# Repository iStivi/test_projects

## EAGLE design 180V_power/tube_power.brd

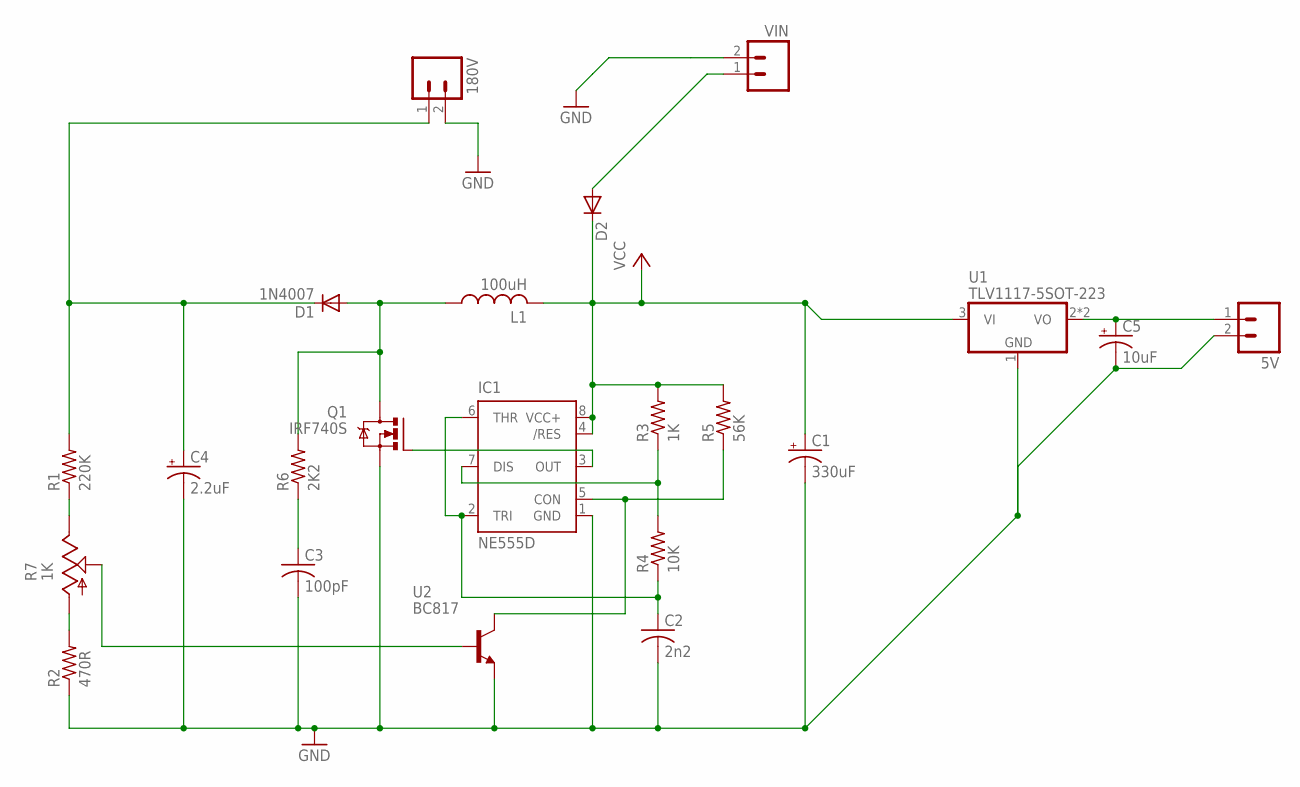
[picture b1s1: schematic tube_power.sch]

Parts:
5V, 180V: M023.5MM; SCREWTERMINAL-3.5MM-2
C1: 330uF; E5-10,5
C2: 2n2; C0805K
C3: 100pF; C0805K
C4: 2.2uF; E5-10,5
C5: 10uF; E2-5
D1: 1N4007; SMA-DIODE
D2: DIODESMA; SMA-DIODE
IC1: NE555D; SO08
L1: 100uH; RBL0712
Q1: IRF740S; TO263
R1: 220K; 0207/10
R2: 470R; 0207/10
R3: 1K; R0805
R4: 10K; R0805
R5: 56K; R0805
R6: 2K2; R0805
R7: 1K; CA6V
U1: TLV1117-5SOT-223; SOT-223
U2: BC817; SOT-23
VIN: M023.5MM; SCREWTERMINAL-3.5MM-2

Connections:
5V: 5V.1, C5.+, U1.2 (VO), U1.4 (VO)
180V: 180V.1, C4.+, D1.C, R1.2
CON: IC1.5 (CON), R5.1, U2.3 (C)
DIS: IC1.7 (DIS), R3.1, R4.2
GND: 5V.2, 180V.2, C1.-, C2.2, C3.2, C4.-, C5.-, IC1.1 (GND), Q1.2 (S), R2.1, U1.1 (GND), U2.2 (E), VIN.2
L1: D1.A, L1.P$1 (1), Q1.3 (D), R6.2
unnamed: D2.A, VIN.1
OUT: IC1.3 (OUT), Q1.1 (G)
R1: R1.1, R7.E
R2: R2.2, R7.A
R6: C3.1, R6.1
THR: C2.1, IC1.2 (TRI), IC1.6 (THR), R4.1
VAR: R7.S, U2.1 (B)
VCC: C1.+, D2.C, IC1.4 (/RES), IC1.8 (VCC+), L1.P$2 (2), R3.2, R5.2, U1.3 (VI)

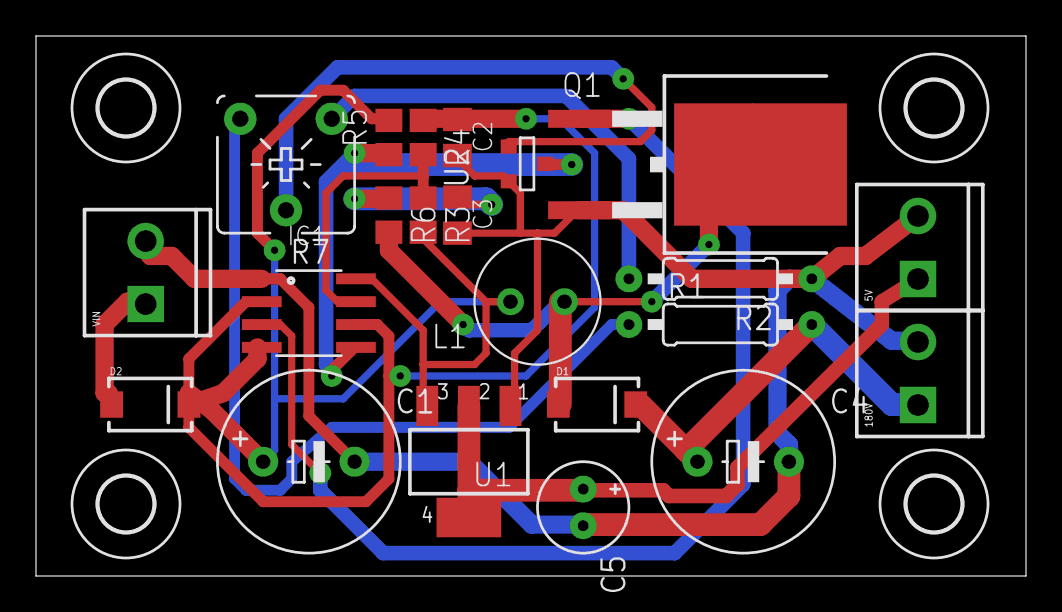
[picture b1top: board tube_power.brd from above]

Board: 2 copper layers, 55.0 x 30.0 mm, 28 parts (1 on the bottom side), 14 nets.

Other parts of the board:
U$1, U$2, U$4, U$5: 3,0-SMALL
U$3: BUZZBOY-SILK
U$6: BUZZBOY

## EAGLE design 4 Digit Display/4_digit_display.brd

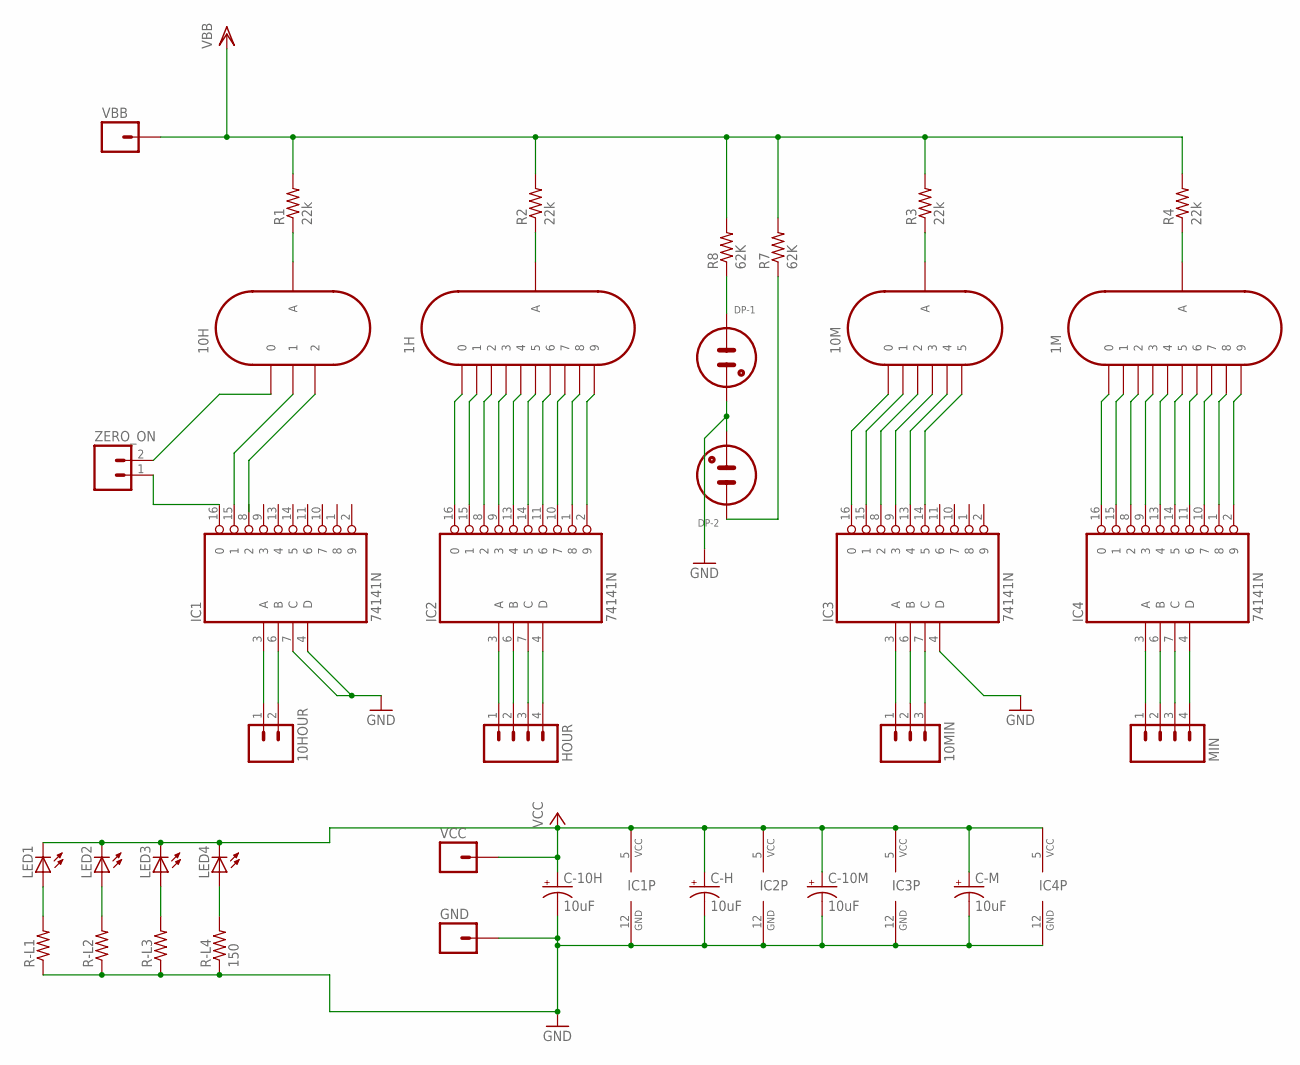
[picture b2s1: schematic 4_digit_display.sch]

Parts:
1H, 1M: IN-12A-NO_DP; IN-12_NO-DP
10H: IN-12_2DIGIT
10HOUR: M02PTH; 1X02
10M: IN-12_6DIGIT
10MIN: M03PTH; 1X03
C-10H, C-10M: 10uF; B/3528-21R
C-H: 10uF; B/3528-21R
C-M: 10uF; B/3528-21R
DP-1, DP-2: INS-1
GND: M01PTH; 1X01
HOUR: M04PTH; 1X04
IC1, IC2, IC3, IC4: 74141N; DIL16
LED1, LED2, LED3, LED4: LED1210
MIN: M04PTH; 1X04
R1, R2, R3, R4: 22k; 0207/10
R7, R8: 62K; 0207/10
R-L1, R-L2, R-L3: RESISTORR1206; R1206
R-L4: 150; R1206
VBB: M01PTH; 1X01
VCC: M01PTH; 1X01
ZERO_ON: M02PTH; 1X02

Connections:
GND: C-10H.-, C-10M.-, C-H.-, C-M.-, DP-1.K, DP-2.K, GND.1, IC1.4 (D), IC1.7 (C), IC1.12 (GND), IC2.12 (GND), IC3.4 (D), IC3.12 (GND), IC4.12 (GND), R-L1.1, R-L2.1, R-L3.1, R-L4.1
unnamed: 1M.0, IC4.16 (0)
unnamed: 1M.1, IC4.15 (1)
unnamed: 1M.2, IC4.8 (2)
unnamed: 1M.3, IC4.9 (3)
unnamed: 1M.4, IC4.13 (4)
unnamed: 1M.5, IC4.14 (5)
unnamed: 1M.6, IC4.11 (6)
unnamed: 1M.7, IC4.10 (7)
unnamed: 1M.8, IC4.1 (8)
unnamed: 1M.9, IC4.2 (9)
unnamed: 10M.0, IC3.16 (0)
unnamed: 10M.1, IC3.15 (1)
unnamed: 10M.2, IC3.8 (2)
unnamed: 10M.3, IC3.9 (3)
unnamed: 10M.4, IC3.13 (4)
unnamed: 10M.5, IC3.14 (5)
unnamed: 1H.0, IC2.16 (0)
unnamed: 1H.1, IC2.15 (1)
unnamed: 1H.2, IC2.8 (2)
unnamed: 1H.3, IC2.9 (3)
unnamed: 1H.4, IC2.13 (4)
unnamed: 1H.5, IC2.14 (5)
unnamed: 1H.6, IC2.11 (6)
unnamed: 1H.7, IC2.10 (7)
unnamed: 1H.8, IC2.1 (8)
unnamed: 1H.9, IC2.2 (9)
unnamed: 10H.1, IC1.15 (1)
unnamed: DP-1.A, R8.1
unnamed: DP-2.A, R7.1
unnamed: IC4.3 (A), MIN.1
unnamed: 1M.A, R4.1
unnamed: 10M.A, R3.1
unnamed: 1H.A, R2.1
unnamed: 10H.A, R1.1
unnamed: IC4.6 (B), MIN.2
unnamed: IC4.7 (C), MIN.3
unnamed: IC4.4 (D), MIN.4
unnamed: 10MIN.1, IC3.3 (A)
unnamed: 10MIN.2, IC3.6 (B)
unnamed: 10MIN.3, IC3.7 (C)
unnamed: HOUR.1, IC2.3 (A)
unnamed: HOUR.2, IC2.6 (B)
unnamed: HOUR.3, IC2.7 (C)
unnamed: HOUR.4, IC2.4 (D)
unnamed: 10HOUR.1, IC1.3 (A)
unnamed: 10HOUR.2, IC1.6 (B)
unnamed: IC1.16 (0), ZERO_ON.1
unnamed: 10H.0, ZERO_ON.2
unnamed: LED1.A, R-L1.2
unnamed: LED2.A, R-L2.2
unnamed: LED3.A, R-L3.2
unnamed: LED4.A, R-L4.2
VBB: R1.2, R2.2, R3.2, R4.2, R7.2, R8.2, VBB.1
VCC: C-10H.+, C-10M.+, C-H.+, C-M.+, IC1.5 (VCC), IC2.5 (VCC), IC3.5 (VCC), IC4.5 (VCC), LED1.C, LED2.C, LED3.C, LED4.C, VCC.1

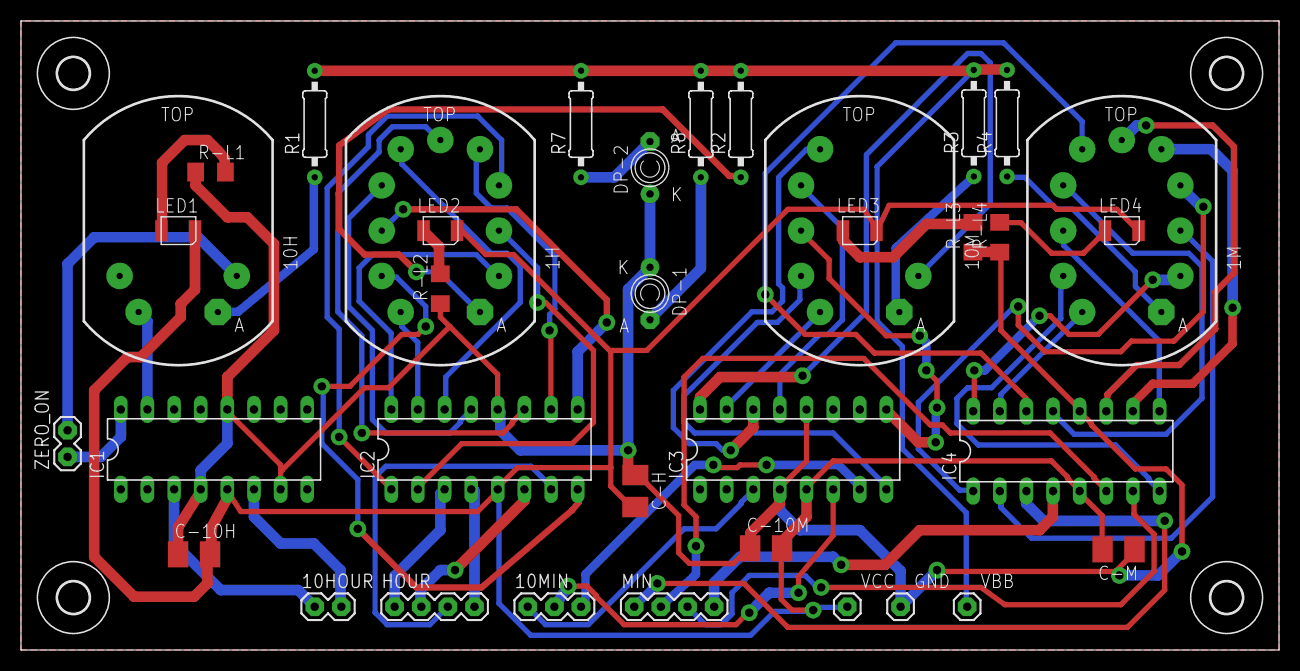
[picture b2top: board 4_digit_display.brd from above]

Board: 2 copper layers, 120.0 x 60.0 mm, 40 parts (0 on the bottom side), 55 nets.

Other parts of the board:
U$2, U$3, U$4, U$5: 3,0

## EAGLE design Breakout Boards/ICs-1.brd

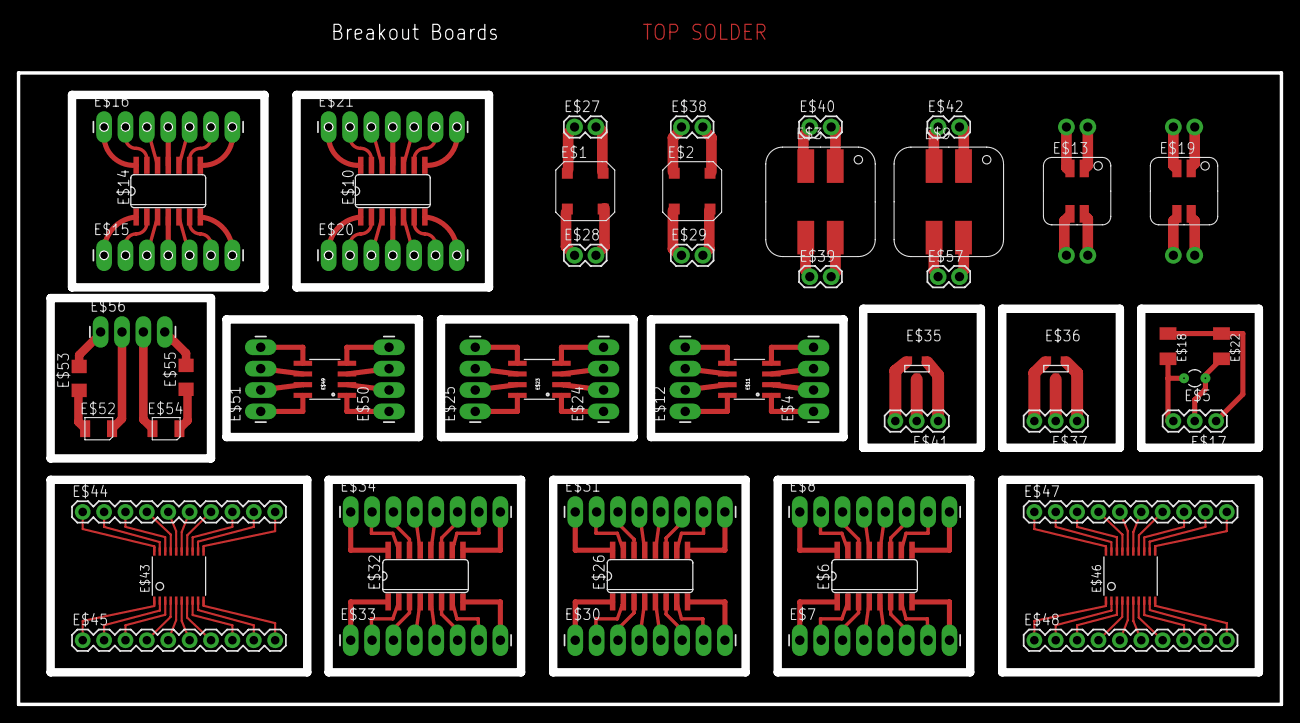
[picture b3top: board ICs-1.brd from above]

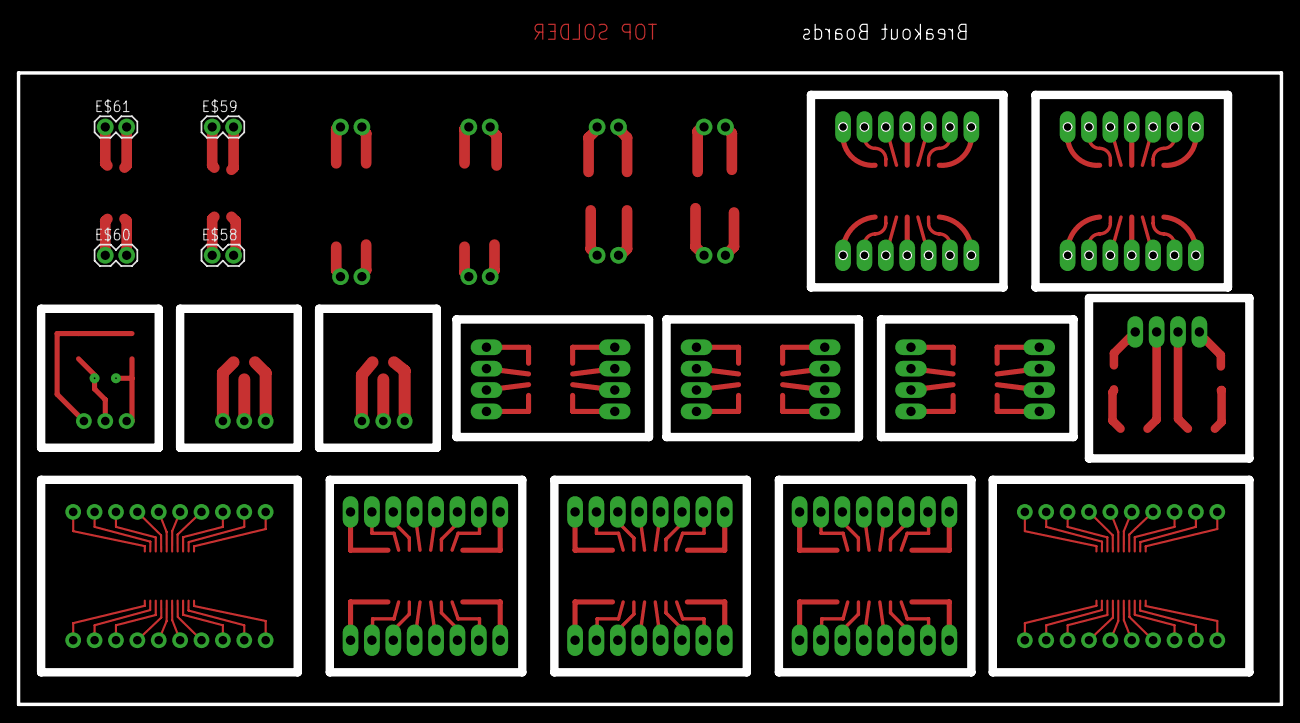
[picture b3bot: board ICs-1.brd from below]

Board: 2 copper layers, 150.0 x 75.0 mm, 61 parts (4 on the bottom side), 129 nets.

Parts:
E$1, E$2: LPR6235
E$3, E$9: MSD1260
E$4, E$12, E$24, E$25, E$50, E$51, E$56: 1X04_LONGPADS
E$5: TC26V
E$6, E$26, E$32: SO16
E$7, E$8, E$30, E$31, E$33, E$34: 1X08_LONGPADS
E$10, E$14: SO14
E$11, E$23, E$49: SO08
E$13, E$19: MSD7342
E$15, E$16, E$20, E$21: 1X07_LONGPADS
E$17, E$37, E$41: 1X03
E$18, E$22: C1206K
E$27, E$28, E$29, E$38, E$39, E$40, E$42, E$57, E$58, E$59, E$60, E$61: 1X02
E$35, E$36: SOT-23
E$43, E$46: TSSOP20
E$44, E$45, E$47, E$48: 1X10
E$52, E$54: LED1210
E$53, E$55: R1206

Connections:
S$15: E$14.1, E$15.1
S$16: E$14.2, E$15.2
S$17: E$6.16, E$8.1
S$18: E$6.15, E$8.2
S$19: E$6.14, E$8.3
S$20: E$6.13, E$8.4
S$21: E$6.12, E$8.5
S$22: E$6.11, E$8.6
S$23: E$6.10, E$8.7
S$24: E$6.9, E$8.8
S$25: E$6.1, E$7.1
S$26: E$6.2, E$7.2
S$27: E$6.3, E$7.3
S$28: E$6.4, E$7.4
S$29: E$6.5, E$7.5
S$30: E$6.7, E$7.7
S$31: E$6.6, E$7.6
S$32: E$6.8, E$7.8
S$33: E$17.3, E$18.2
S$34: E$17.2, E$22.2
S$35: E$17.1, E$18.1, E$22.1
S$36: E$14.3, E$15.3
S$37: E$14.4, E$15.4
S$39: E$14.5, E$15.5
S$40: E$14.6, E$15.6
S$49: E$14.7, E$15.7
S$50: E$14.14, E$16.1
S$51: E$14.13, E$16.2
S$52: E$14.12, E$16.3
S$53: E$14.11, E$16.4
S$54: E$14.10, E$16.5
S$55: E$14.9, E$16.6
S$56: E$14.8, E$16.7
S$57: E$23.8, E$25.1
S$58: E$23.7, E$25.2
S$59: E$23.6, E$25.3
S$60: E$23.5, E$25.4
S$61: E$23.1, E$24.1
S$62: E$23.2, E$24.2
S$63: E$11.8, E$12.1
S$64: E$11.7, E$12.2
S$65: E$11.6, E$12.3
S$66: E$11.5, E$12.4
S$67: E$4.1, E$11.1
S$68: E$4.2, E$11.2
S$69: E$4.3, E$11.3
S$70: E$4.4, E$11.4
S$91: E$10.1, E$20.1
S$92: E$10.2, E$20.2
S$93: E$10.3, E$20.3
S$94: E$10.4, E$20.4
S$95: E$10.5, E$20.5
S$96: E$10.6, E$20.6
S$97: E$10.7, E$20.7
S$98: E$10.14, E$21.1
S$99: E$10.13, E$21.2
S$100: E$10.12, E$21.3
S$101: E$10.11, E$21.4
S$102: E$10.10, E$21.5
S$103: E$10.9, E$21.6
S$104: E$10.8, E$21.7
S$105: E$23.3, E$24.3
S$106: E$23.4, E$24.4
S$108: E$26.16, E$31.1
S$109: E$26.15, E$31.2
S$110: E$26.14, E$31.3
S$111: E$26.13, E$31.4
S$123: E$26.12, E$31.5
S$124: E$26.11, E$31.6
S$125: E$26.10, E$31.7
S$126: E$26.9, E$31.8
S$127: E$26.1, E$30.1
S$128: E$26.2, E$30.2
S$129: E$26.3, E$30.3
S$130: E$26.4, E$30.4
S$131: E$26.5, E$30.5
S$132: E$26.7, E$30.7
S$133: E$26.6, E$30.6
S$134: E$26.8, E$30.8
S$135: E$32.16, E$34.1
S$136: E$32.15, E$34.2
S$137: E$32.14, E$34.3
S$138: E$32.13, E$34.4
S$139: E$32.12, E$34.5
S$140: E$32.11, E$34.6
S$141: E$32.10, E$34.7
S$142: E$32.9, E$34.8
S$143: E$32.1, E$33.1
S$144: E$32.2, E$33.2
S$145: E$32.3, E$33.3
S$146: E$32.4, E$33.4
S$147: E$32.5, E$33.5
S$148: E$32.7, E$33.7
S$149: E$32.6, E$33.6
S$150: E$32.8, E$33.8
S$157: E$43.20, E$44.1
S$158: E$43.19, E$44.2
S$159: E$43.18, E$44.3
S$160: E$43.17, E$44.4
S$161: E$43.16, E$44.5
S$162: E$43.15, E$44.6
S$163: E$43.14, E$44.7
S$164: E$43.12, E$44.9
S$165: E$43.13, E$44.8
S$166: E$43.11, E$44.10
S$167: E$46.20, E$47.1
S$168: E$46.19, E$47.2
S$169: E$46.18, E$47.3
S$170: E$46.17, E$47.4
S$171: E$46.16, E$47.5
S$172: E$46.15, E$47.6
S$173: E$46.14, E$47.7
S$174: E$46.12, E$47.9
S$175: E$46.13, E$47.8
S$176: E$46.11, E$47.10
S$197: E$49.8, E$51.1
S$198: E$49.7, E$51.2
S$199: E$49.6, E$51.3
S$200: E$49.5, E$51.4
S$201: E$49.1, E$50.1
S$202: E$49.2, E$50.2
S$203: E$49.3, E$50.3
S$204: E$49.4, E$50.4
S$205: E$53.2, E$56.1
S$206: E$52.A, E$53.1
S$207: E$52.C, E$56.2
S$208: E$54.A, E$56.3
S$209: E$54.C, E$55.1
S$210: E$55.2, E$56.4

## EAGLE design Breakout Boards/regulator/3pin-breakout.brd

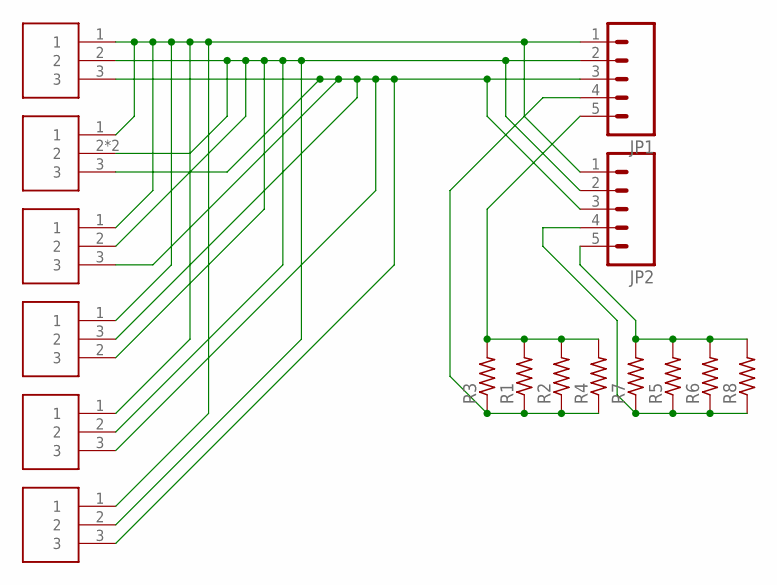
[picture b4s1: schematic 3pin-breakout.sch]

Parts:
JP1, JP2: M05PTH; 1X05
R1, R3, R5, R7: RESISTORR0805; R0805
R2, R4, R6, R8: RESISTORR1206; R1206
U$1: BLANK-3PINSOT23; SOT-23
U$2: BLANK-3PINSOT223; SOT-223
U$3: BLANK-3PINSOT323; SC70
U$4: BLANK-3PINSOT416; SC75_INFINEON
U$5: BLANK-3PINTO252; TO252
U$6: BLANK-3PINTO263; TO263

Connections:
unnamed: JP1.1, JP2.1, U$1.1, U$2.1, U$3.1, U$4.1, U$5.1, U$6.1
unnamed: JP1.2, JP2.2, U$1.2, U$2.2, U$2.4 (2), U$3.2, U$4.2 (3), U$5.2, U$6.2
unnamed: JP1.3, JP2.3, U$1.3, U$2.3, U$3.3, U$4.3 (2), U$5.3, U$6.3
unnamed: JP1.5, R1.2, R2.2, R3.2, R4.2
unnamed: JP1.4, R1.1, R2.1, R3.1, R4.1
unnamed: JP2.5, R5.2, R6.2, R7.2, R8.2
unnamed: JP2.4, R5.1, R6.1, R7.1, R8.1

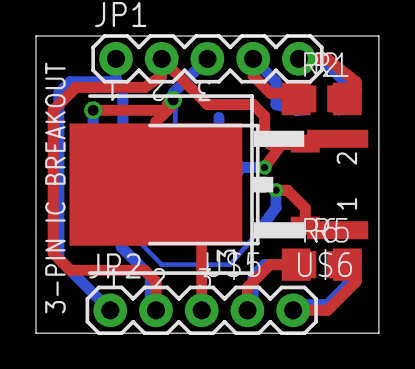
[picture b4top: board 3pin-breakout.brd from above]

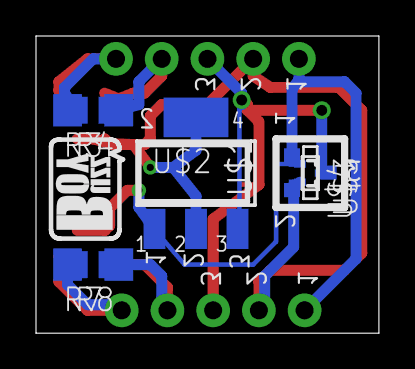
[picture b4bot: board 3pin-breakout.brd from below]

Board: 2 copper layers, 19.1 x 16.5 mm, 17 parts (8 on the bottom side), 7 nets.

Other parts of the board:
U$7: BUZZBOY-SILK-BOTTOM

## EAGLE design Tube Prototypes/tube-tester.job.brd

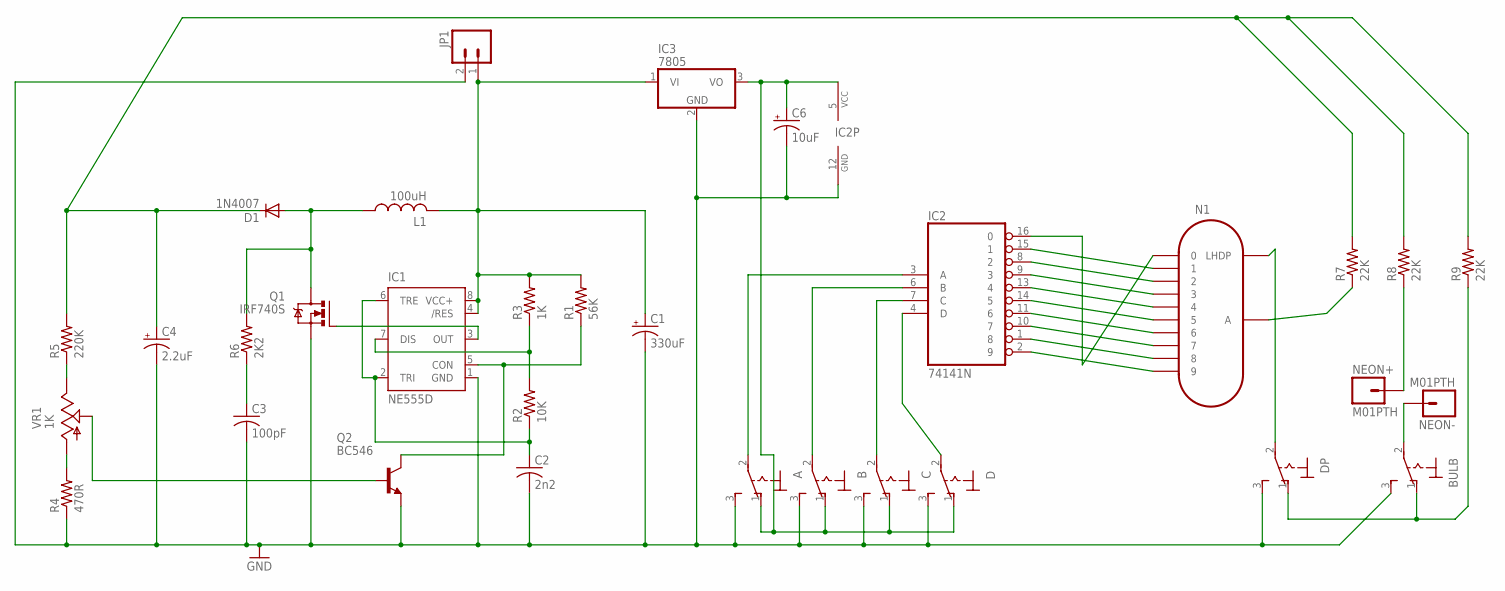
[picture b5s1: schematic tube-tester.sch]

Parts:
A: 320-916
B: 320-916
BULB: 320-916
C: 320-916
C1: 330uF; E5-10,5
C2: 2n2; C1206K
C3: 100pF; C1206K
C4: 2.2uF; E3,5-8
C6: 10uF; E2-5
D: 320-916
D1: 1N4007; SMA-DIODE
DP: 320-916
IC1: NE555D; SO08
IC2: 74141N; DIL16
IC3: 7805; TO220H
JP1: M023.5MM; SCREWTERMINAL-3.5MM-2
L1: 100uH; 0207/10
N1: IN-12B; IN-12
NEON+: M01PTH; 1X01
NEON-: M01PTH; 1X01
Q1: IRF740S; TO263
Q2: BC546; TO92-EBC
R1: 56K; R1206
R2: 10K; R1206
R3: 1K; R1206
R4: 470R; 0207/10
R5: 220K; 0207/10
R6: 2K2; R1206
R7, R8, R9: 22K; 0207/10
VR1: 1K; CA6V

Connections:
GND: A.3 (S), B.3 (S), BULB.3 (S), C.3 (S), C1.-, C2.2, C3.2, C4.-, C6.-, D.3 (S), DP.3 (S), IC1.1 (GND), IC2.12 (GND), IC3.2 (GND), JP1.2, Q1.2 (S), Q2.E, R4.1
unnamed: IC1.3 (OUT), Q1.1 (G)
unnamed: C3.1, R6.1
unnamed: IC1.5 (CON), Q2.C, R1.1
unnamed: IC1.7 (DIS), R2.2, R3.1
unnamed: C2.1, IC1.2 (TRI), IC1.6 (TRE), R2.1
unnamed: D1.A, L1.1, Q1.3 (D), R6.2
unnamed: C4.+, D1.C, R5.2, R7.2, R8.2, R9.2
unnamed: R5.1, VR1.E
unnamed: R4.2, VR1.A
unnamed: Q2.B, VR1.S
unnamed: IC2.15 (1), N1.1
unnamed: IC2.8 (2), N1.2
unnamed: IC2.9 (3), N1.3
unnamed: IC2.13 (4), N1.4
unnamed: IC2.14 (5), N1.5
unnamed: IC2.11 (6), N1.6
unnamed: IC2.10 (7), N1.7
unnamed: IC2.1 (8), N1.8
unnamed: IC2.2 (9), N1.9
unnamed: IC2.16 (0), N1.0
unnamed: N1.A, R7.1
unnamed: A.2, IC2.3 (A)
unnamed: B.2, IC2.6 (B)
unnamed: C.2, IC2.7 (C)
unnamed: D.2, IC2.4 (D)
unnamed: C1.+, IC1.4 (/RES), IC1.8 (VCC+), IC3.1 (VI), JP1.1, L1.2, R1.2, R3.2
unnamed: NEON+.1, R8.1
unnamed: BULB.2, NEON-.1
unnamed: A.1 (O), B.1 (O), C.1 (O), C6.+, D.1 (O), IC2.5 (VCC), IC3.3 (VO)
unnamed: DP.2, N1.LHDP
unnamed: BULB.1 (O), DP.1 (O), R9.1

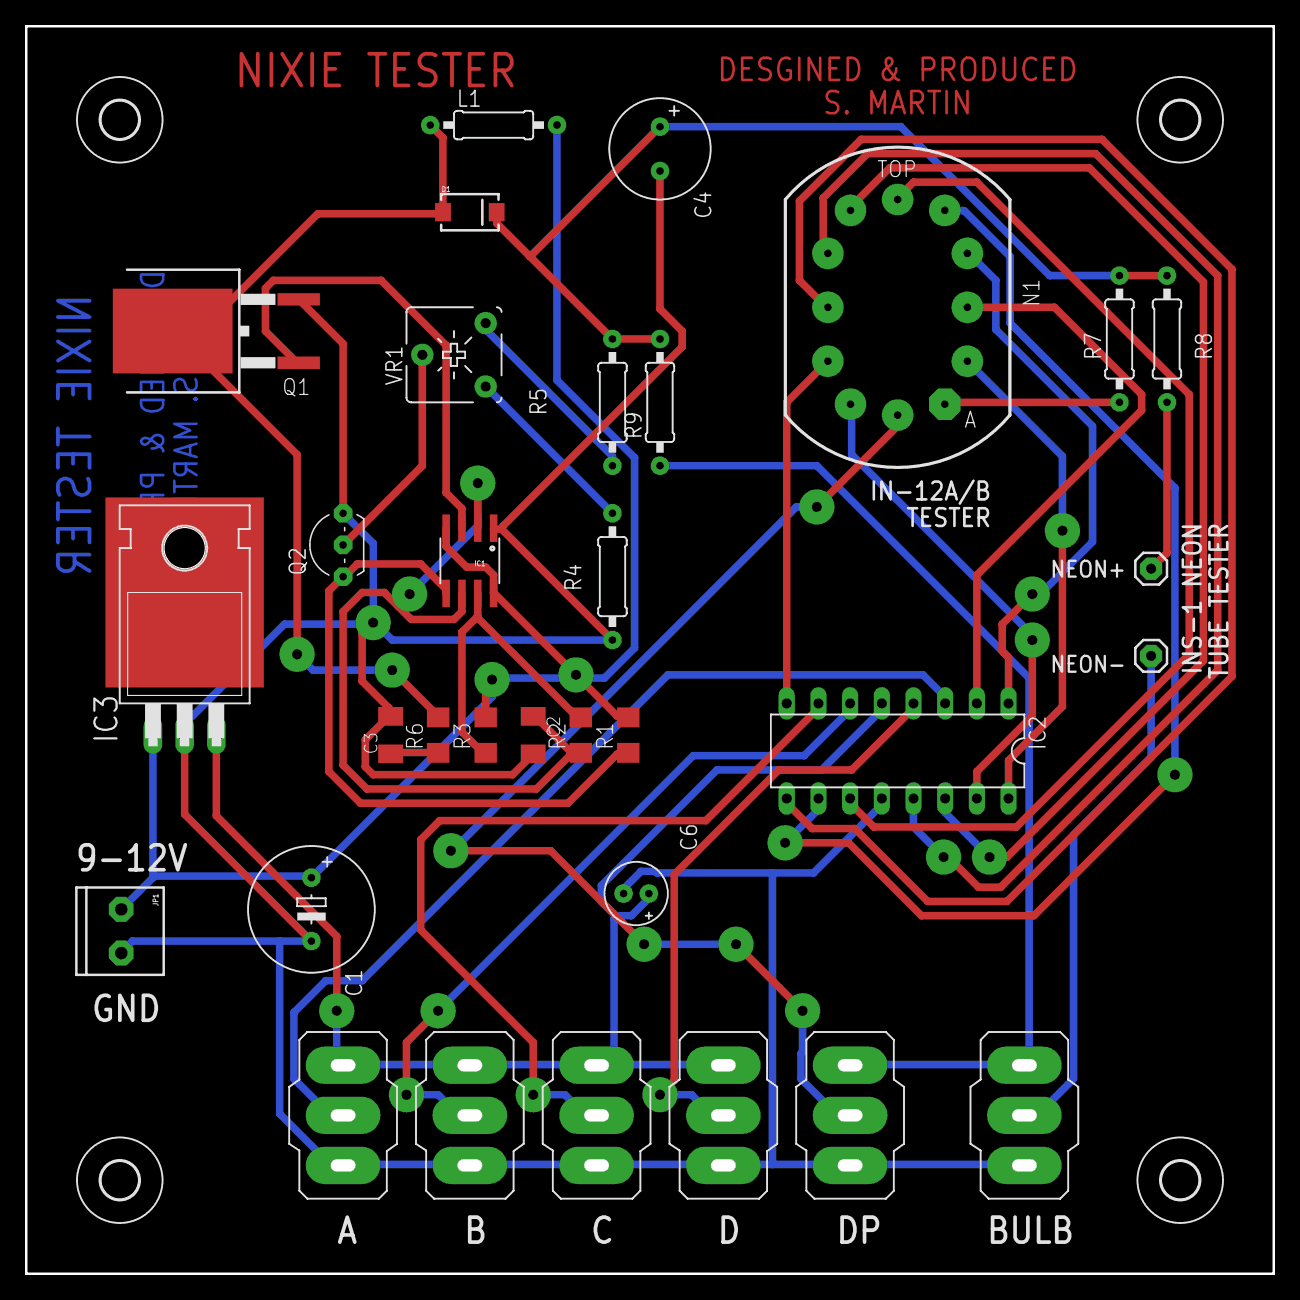
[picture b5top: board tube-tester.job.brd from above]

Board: 2 copper layers, 100.0 x 100.0 mm, 36 parts (0 on the bottom side), 32 nets.

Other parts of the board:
U$1, U$2, U$3, U$4: 3,0

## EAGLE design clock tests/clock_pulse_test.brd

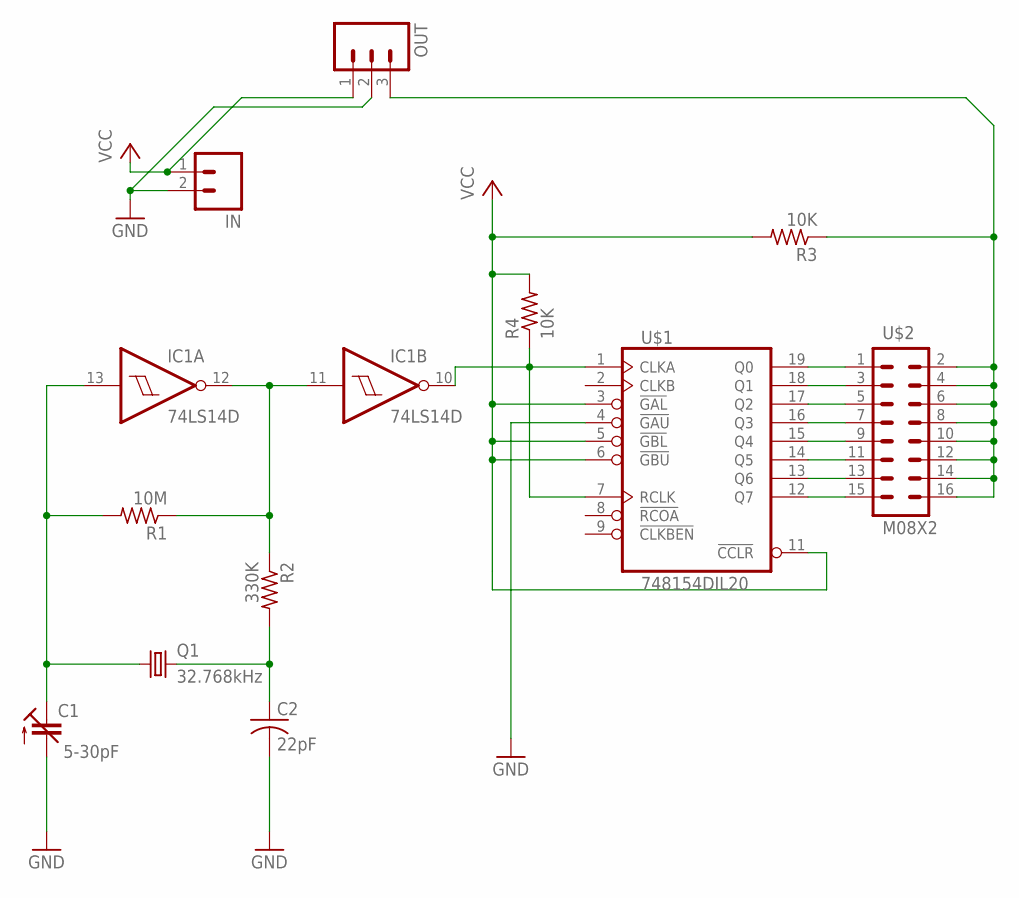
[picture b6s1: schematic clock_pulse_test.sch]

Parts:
C1: 5-30pF; CTRIMTZ03
C2: 22pF; C050-024X044
IC1: 74LS14D; SO14
IN: M02PTH; 1X02
OUT: M03PTH; 1X03
Q1: 32.768kHz; TC26V
R1: 10M; 0207/10
R2: 330K; 0207/10
R3, R4: 10K; 0207/10
U$1: 748154DIL20; DIL20
U$2: M08X2; 2X8

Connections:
GND: C1.2 (A), C2.2, IC1.7 (GND), IN.2, OUT.2, U$1.4 (!GAU), U$1.10 (GND)
unnamed: U$1.19 (Q0), U$2.1
unnamed: U$1.18 (Q1), U$2.3
unnamed: U$1.17 (Q2), U$2.5
unnamed: U$1.16 (Q3), U$2.7
unnamed: U$1.15 (Q4), U$2.9
unnamed: U$1.14 (Q5), U$2.11
unnamed: U$1.13 (Q6), U$2.13
unnamed: U$1.12 (Q7), U$2.15
unnamed: C1.1 (E), IC1.13 (I), Q1.1, R1.2
unnamed: C2.1, Q1.2, R2.2
unnamed: IC1.11 (I), IC1.12 (O), R1.1, R2.1
unnamed: IC1.10 (O), R4.1, U$1.1 (CLKA), U$1.7 (RCLK)
unnamed: OUT.3, R3.1, U$2.2, U$2.4, U$2.6, U$2.8, U$2.10, U$2.12, U$2.14, U$2.16
VCC: IC1.14 (VCC), IN.1, OUT.1, R3.2, R4.2, U$1.3 (!GAL), U$1.5 (!GBL), U$1.6 (!GBU), U$1.11 (!CCLR), U$1.20 (VCC)

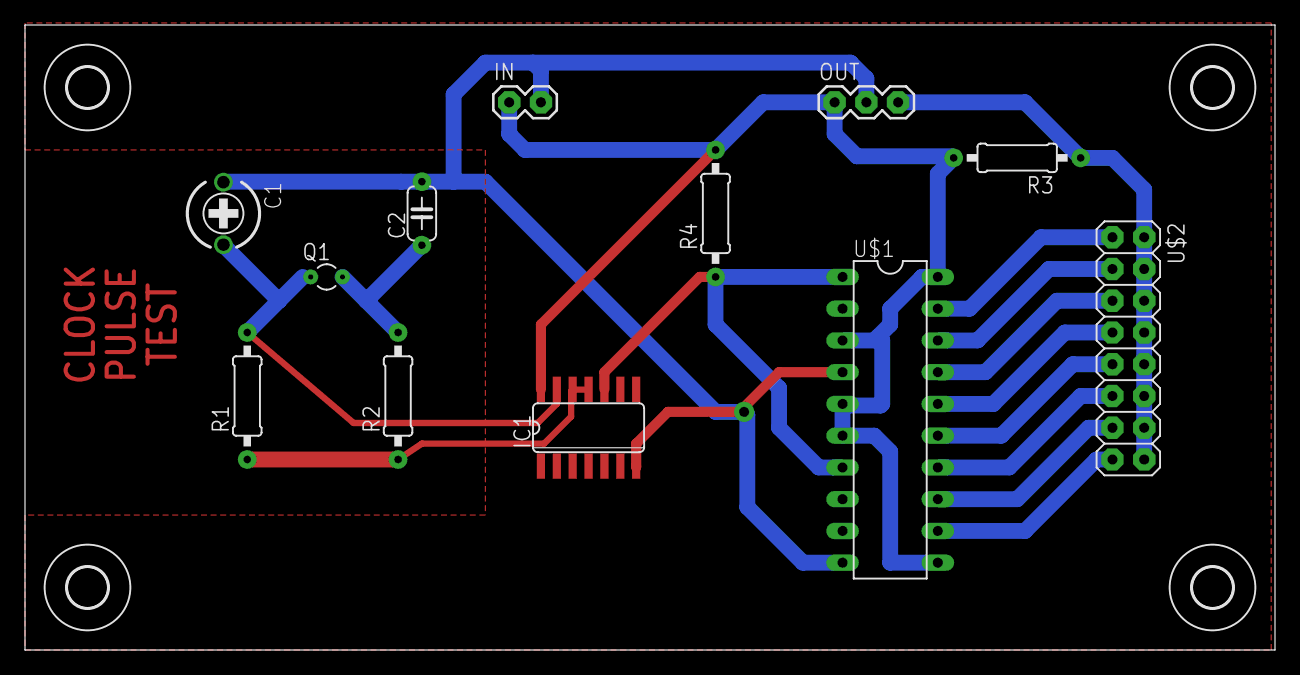
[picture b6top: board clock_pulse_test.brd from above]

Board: 2 copper layers, 100.0 x 50.0 mm, 16 parts (0 on the bottom side), 15 nets.

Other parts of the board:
U$3, U$4, U$5, U$6: 3,2

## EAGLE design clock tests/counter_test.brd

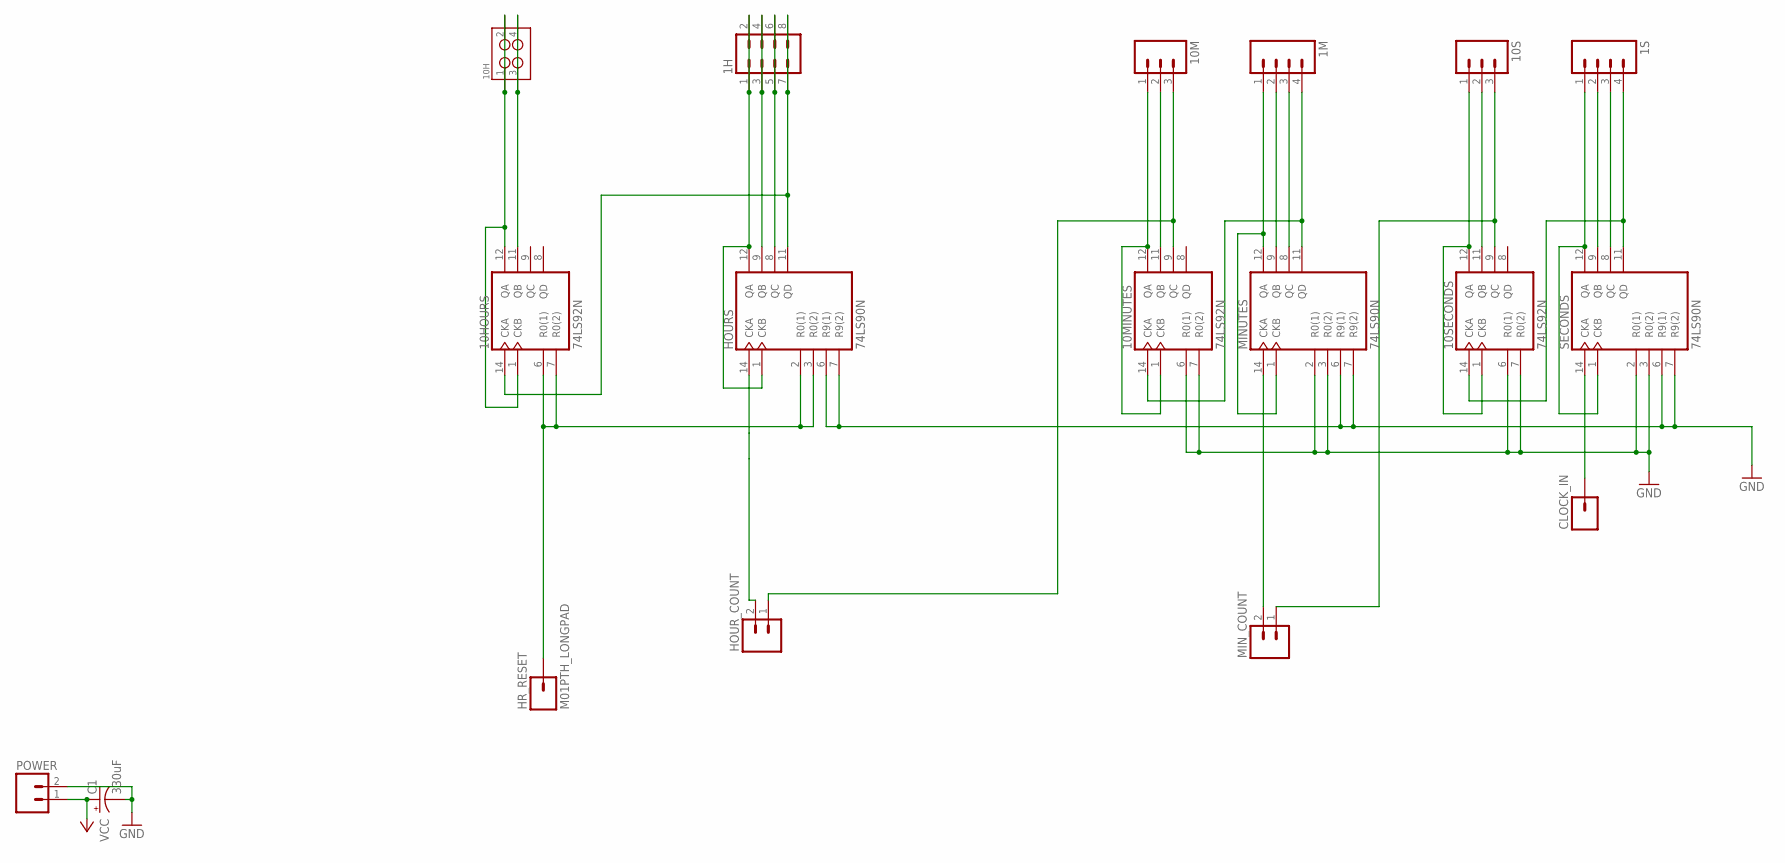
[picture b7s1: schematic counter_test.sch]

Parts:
1H: M04X2; 2X4
1M, 1S: M04LONGPADS; 1X04_LONGPADS
10H: M02X2; 2X2
10HOURS, 10MINUTES, 10SECONDS: 74LS92N; DIL14
10M, 10S: M03LONGPADS; 1X03_LONGPADS
C1: 330uF; E3,5-8
CLOCK_IN: M01PTH_LONGPAD; 1X01_LONGPAD
HOURS: 74LS90N; DIL14
HOUR_COUNT: M02PTH3; 1X02_LONGPADS
HR_RESET: M01PTH_LONGPAD; 1X01_LONGPAD
MINUTES: 74LS90N; DIL14
MIN_COUNT: M02PTH3; 1X02_LONGPADS
POWER: M02PTH3; 1X02_LONGPADS
SECONDS: 74LS90N; DIL14

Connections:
1H_A: 1H.1, 1H.2, HOURS.1 (CKB), HOURS.12 (QA)
1H_B: 1H.3, 1H.4, HOURS.9 (QB)
1H_C: 1H.5, 1H.6, HOURS.8 (QC)
1H_D: 1H.7, 1H.8, 10HOURS.14 (CKA), HOURS.11 (QD)
1M_A: 1M.1, MINUTES.1 (CKB), MINUTES.12 (QA)
1M_B: 1M.2, MINUTES.9 (QB)
1M_C: 1M.3, MINUTES.8 (QC)
1M_D: 1M.4, 10MINUTES.14 (CKA), MINUTES.11 (QD)
1S_A: 1S.1, SECONDS.1 (CKB), SECONDS.12 (QA)
1S_B: 1S.2, SECONDS.9 (QB)
1S_C: 1S.3, SECONDS.8 (QC)
1S_D: 1S.4, 10SECONDS.14 (CKA), SECONDS.11 (QD)
10H_A: 10H.1, 10H.2, 10HOURS.1 (CKB), 10HOURS.12 (QA)
10H_B: 10H.3, 10H.4, 10HOURS.11 (QB)
10M_A: 10M.1, 10MINUTES.1 (CKB), 10MINUTES.12 (QA)
10M_B: 10M.2, 10MINUTES.11 (QB)
10M_C: 10M.3, 10MINUTES.9 (QC), HOUR_COUNT.1
10S_A: 10S.1, 10SECONDS.1 (CKB), 10SECONDS.12 (QA)
10S_B: 10S.2, 10SECONDS.11 (QB)
10S_C: 10S.3, 10SECONDS.9 (QC), MIN_COUNT.1
GND: 10HOURS.10 (GND), 10MINUTES.6 (R0(1)), 10MINUTES.7 (R0(2)), 10MINUTES.10 (GND), 10SECONDS.6 (R0(1)), 10SECONDS.7 (R0(2)), 10SECONDS.10 (GND), C1.-, HOURS.6 (R9(1)), HOURS.7 (R9(2)), HOURS.10 (GND), MINUTES.2 (R0(1)), MINUTES.3 (R0(2)), MINUTES.6 (R9(1)), MINUTES.7 (R9(2)), MINUTES.10 (GND), POWER.2, SECONDS.2 (R0(1)), SECONDS.3 (R0(2)), SECONDS.6 (R9(1)), SECONDS.7 (R9(2)), SECONDS.10 (GND)
HR_RESET: 10HOURS.6 (R0(1)), 10HOURS.7 (R0(2)), HOURS.2 (R0(1)), HOURS.3 (R0(2)), HR_RESET.1
unnamed: MINUTES.14 (CKA), MIN_COUNT.2
unnamed: CLOCK_IN.1, SECONDS.14 (CKA)
unnamed: HOURS.14 (CKA), HOUR_COUNT.2
VCC: 10HOURS.5 (VCC), 10MINUTES.5 (VCC), 10SECONDS.5 (VCC), C1.+, HOURS.5 (VCC), MINUTES.5 (VCC), POWER.1, SECONDS.5 (VCC)

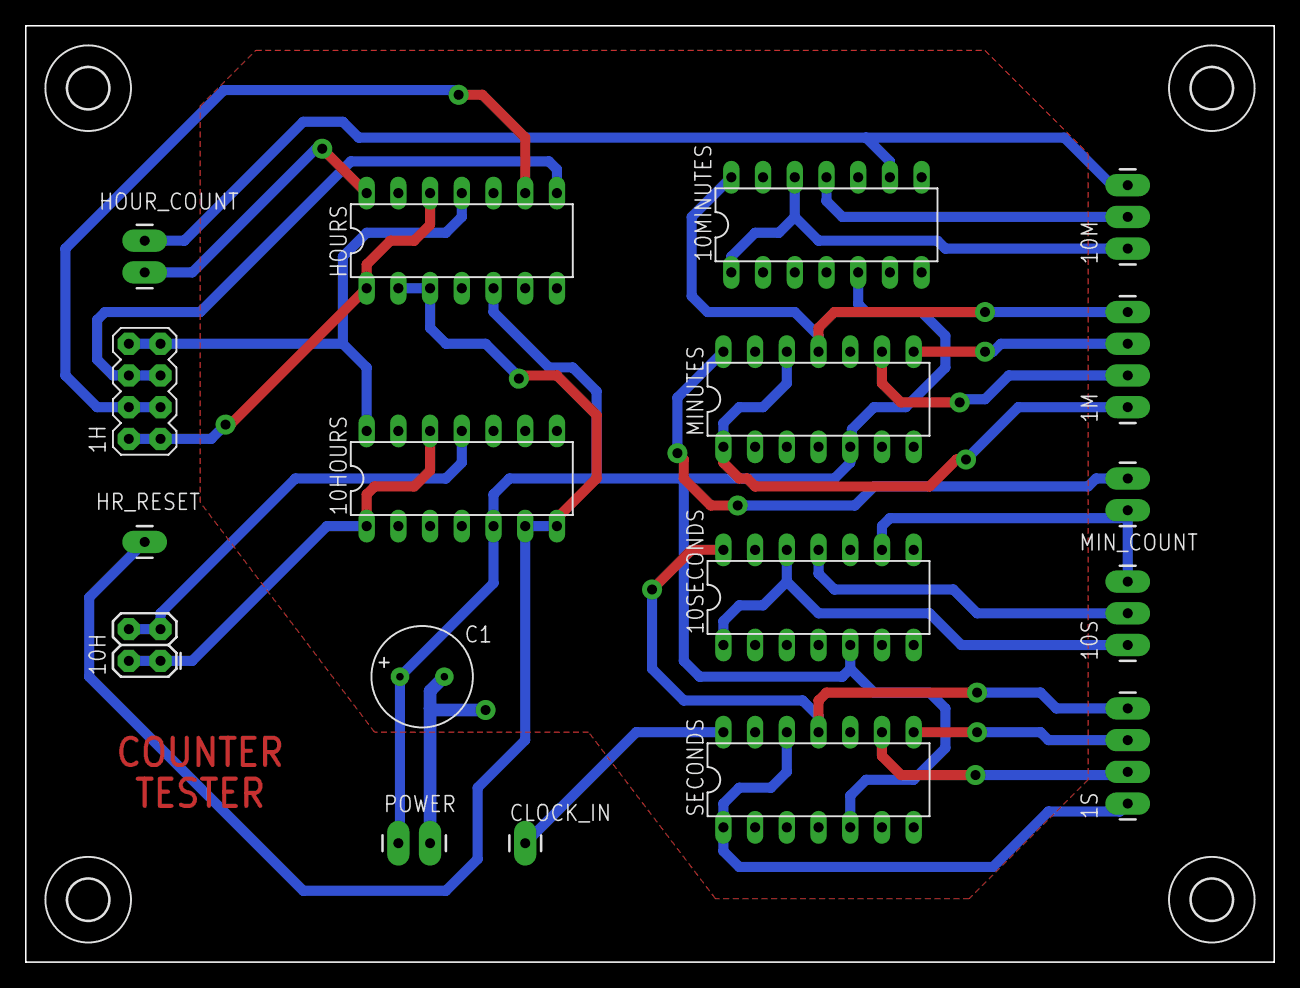
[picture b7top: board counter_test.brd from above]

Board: 2 copper layers, 100.0 x 75.0 mm, 19 parts (0 on the bottom side), 26 nets.

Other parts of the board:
U$1: BOARD-75X100
